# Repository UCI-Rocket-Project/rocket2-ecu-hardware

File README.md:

# rocket2's Engine Control Unit (ECU)
Documenation for ECU is hosted with MKDocs: [Click Here](https://uci-rocket-project.github.io/rocket2-ecu-hardware/)
  
# CAD

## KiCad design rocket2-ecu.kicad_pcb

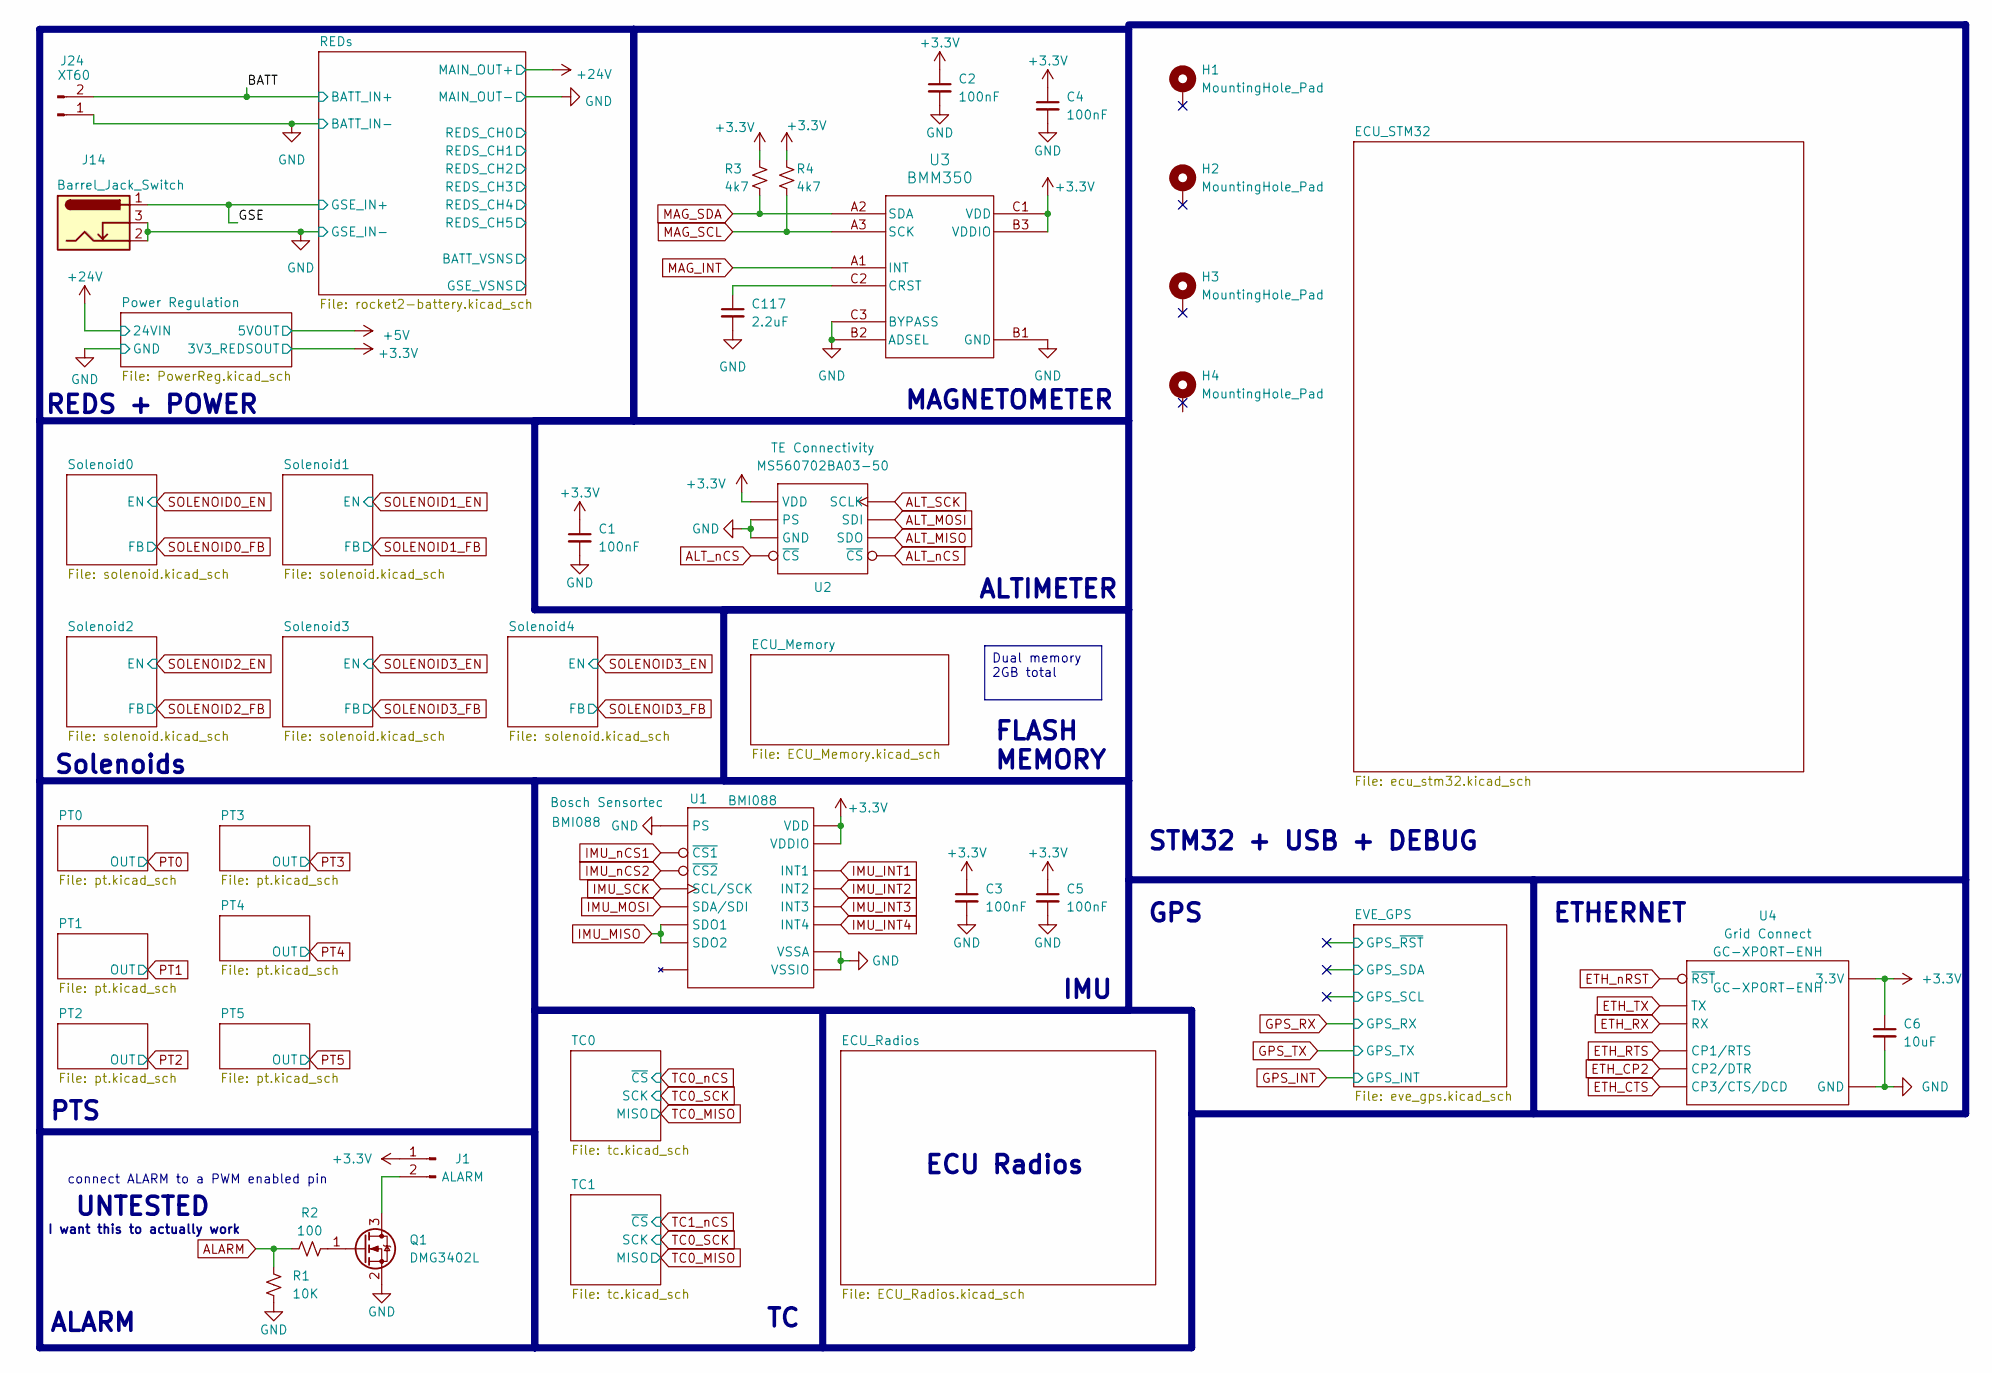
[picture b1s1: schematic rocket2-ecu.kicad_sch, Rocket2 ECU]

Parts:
C1, C2, C3, C4, C5: 100nF; C_0402_1005Metric; Part # Generic CAP CER 0.1UF 6.3V X7R 0402
C6: 10uF; C_0603_1608Metric; Part # Generic CAP CER 10UF 50V X7R 0603
C117: 2.2uF; C_0402_1005Metric; Part # Generic CAP CER 0.1UF 6.3V X7R 0402
H1, H2, H3, H4: MountingHole_Pad; MountingHole_4.3mm_M4_Pad_Via
J1: ALARM; Buzzer_TDK_PS1240P02BT_D12.2mm_H6.5mm; Part # CMI-0955-03TH
J14: Barrel_Jack_Switch; BarrelJack_Horizontal
J24: XT60; AMASS_XT60PW-M_1x02_P7.20mm_Horizontal
Q1: DMG3402L; SOT-23-3; Part # DMG3402L
R1: 10K; R_0402_1005Metric; Part # Generic RES SMD 10K OHM 1% 1/4W 0402
R2: 100; R_0402_1005Metric; Part # Generic RES SMD 100 OHM 1% 1/4W 0402
R3, R4: 4k7; R_0402_1005Metric; Part # Generic RES SMD 4.7K OHM 1% 1/4W 0402
U1: BMI088; Part # BMI088
U2: MS560702BA03-50; MS5607-02BA; Part # MS560702BA03-50
U3: BMM350
U4: GC-XPORT-ENH; GC-XPORT; Part # GC-XPORT-ENH

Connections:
+3.3V: C1.1, C2.1, C3.1, C4.1, C5.1, C6.1, J1.1, R3.1, R4.1, U1.3 (VDD), U1.11 (VDDIO), U2.1 (VDD), U3.B3 (VDDIO), U3.C1 (VDD), U4.2 (3.3V); also elsewhere on the board
/BATT: J24.2; also elsewhere on the board
/GSE: J14.1; also elsewhere on the board
ALARM: R1.2, R2.1; also elsewhere on the board
ALT_MISO: U2.6 (SDO); also elsewhere on the board
ALT_MOSI: U2.7 (SDI); also elsewhere on the board
ALT_SCK: U2.8 (SCLK); also elsewhere on the board
ALT_nCS: U2.4 (~CS), U2.5 (~CS); also elsewhere on the board
ETH_CP2: U4.7 (CP2/DTR); also elsewhere on the board
ETH_CTS: U4.8 (CP3/CTS/DCD); also elsewhere on the board
ETH_RTS: U4.6 (CP1/RTS); also elsewhere on the board
ETH_RX: U4.5 (RX); also elsewhere on the board
ETH_TX: U4.4 (TX); also elsewhere on the board
ETH_nRST: U4.3 (~RST); also elsewhere on the board
GND: C1.2, C2.2, C3.2, C4.2, C5.2, C6.2, C117.2, J14.2, J14.3, J24.1, Q1.2 (S), R1.1, U1.4 (VSSA), U1.6 (VSSIO), U1.7 (PS), U2.2 (PS), U2.3 (GND), U3.B1 (GND), U3.B2 (ADSEL), U3.C3 (BYPASS), U4.1 (GND); also elsewhere on the board
IMU_INT1: U1.16 (INT1); also elsewhere on the board
IMU_INT2: U1.1 (INT2); also elsewhere on the board
IMU_INT3: U1.12 (INT3); also elsewhere on the board
IMU_INT4: U1.13 (INT4); also elsewhere on the board
IMU_MISO: U1.10 (SDO2), U1.15 (SDO1); also elsewhere on the board
IMU_MOSI: U1.9 (SDA/SDI); also elsewhere on the board
IMU_SCK: U1.8 (SCL/SCK); also elsewhere on the board
IMU_nCS1: U1.14 (~CS1); also elsewhere on the board
IMU_nCS2: U1.5 (~CS2); also elsewhere on the board
MAG_INT: U3.A1 (INT); also elsewhere on the board
MAG_SCL: R4.2, U3.A3 (SCK); also elsewhere on the board
MAG_SDA: R3.2, U3.A2 (SDA); also elsewhere on the board
unnamed: J1.2, Q1.3 (D)
unnamed: Q1.1 (G), R2.2
unnamed: C117.1, U3.C2 (CRST)

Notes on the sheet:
connect ALARM to a PWM enabled pin
ECU Radios
ALTIMETER
GPS
Solenoids
REDS + POWER
FLASH MEMORY
MAGNETOMETER
STM32 + USB + DEBUG
UNTESTED
IMU
PTS
ETHERNET
I want this to actually work
ALARM
Dual memory 2GB total

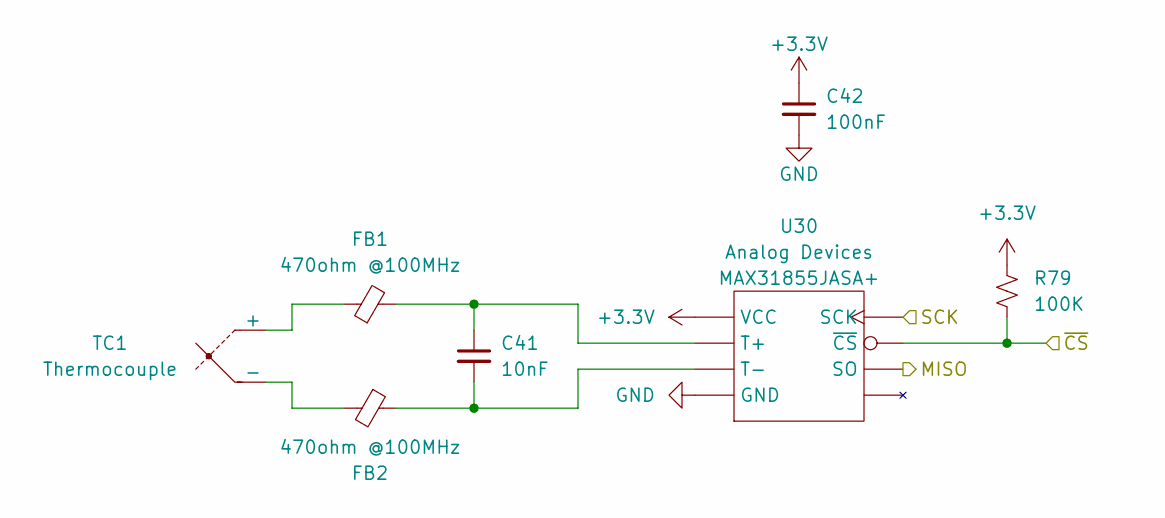
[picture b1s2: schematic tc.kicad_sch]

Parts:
C41: 10nF; C_0402_1005Metric; Part # Generic CAP CER 10NF 6.3V X7R 0402
C42: 100nF; C_0402_1005Metric; Part # Generic CAP CER 0.1UF 6.3V X7R 0402
FB1, FB2: 470ohm @100MHz; L_0603_1608Metric; Part # BLM18PG471SH1D
R79: 100K; R_0402_1005Metric; Part # Generic RES SMD 100K OHM 1% 1/16W 0402
TC1: Thermocouple; AM-K-PCB; Part # AM-K-PCB
U30: SOIC-8_3.9x4.9mm_P1.27mm; Part # MAX31855JASA+

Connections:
+3.3V: C42.1, R79.1, U30.4 (VCC); also elsewhere on the board
GND: C42.2, U30.1 (GND); also elsewhere on the board
unnamed: FB1.1, TC1.1 (+)
unnamed: FB2.2, TC1.2 (-)
unnamed: C41.1, FB1.2, U30.3 (T+)
unnamed: C41.2, FB2.1, U30.2 (T-)
TC0_MISO: U30.7 (SO); also elsewhere on the board
TC0_SCK: U30.5 (SCK); also elsewhere on the board
TC0_nCS: R79.2, U30.6 (~CS); also elsewhere on the board

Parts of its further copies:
C99: 10nF; C_0402_1005Metric; Part # Generic CAP CER 10NF 6.3V X7R 0402
C100: 100nF; C_0402_1005Metric; Part # Generic CAP CER 0.1UF 6.3V X7R 0402
FB3, FB4: 470ohm @100MHz; L_0603_1608Metric; Part # BLM18PG471SH1D
R124: 100K; R_0402_1005Metric; Part # Generic RES SMD 100K OHM 1% 1/16W 0402
TC2: Thermocouple; AM-K-PCB; Part # AM-K-PCB
U49: SOIC-8_3.9x4.9mm_P1.27mm; Part # MAX31855JASA+

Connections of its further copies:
+3.3V: C100.1, R124.1, U49.4 (VCC); also elsewhere on the board
GND: C100.2, U49.1 (GND); also elsewhere on the board
unnamed: FB3.1, TC2.1 (+)
unnamed: FB4.2, TC2.2 (-)
unnamed: C99.1, FB3.2, U49.3 (T+)
unnamed: C99.2, FB4.1, U49.2 (T-)
TC0_MISO: U49.7 (SO); also elsewhere on the board
TC0_SCK: U49.5 (SCK); also elsewhere on the board
TC1_nCS: R124.2, U49.6 (~CS); also elsewhere on the board

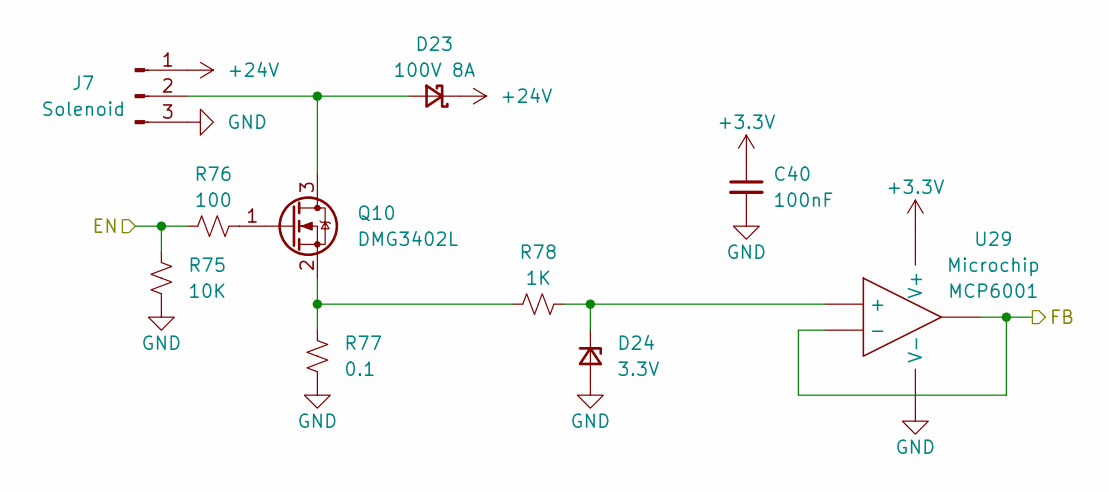
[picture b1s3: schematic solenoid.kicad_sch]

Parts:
C40: 100nF; C_0402_1005Metric; Part # Generic CAP CER 0.1UF 6.3V X7R 0402
D23: 100V 8A; D_PowerDI-5; Part # SDT8A100P5-7
D24: 3.3V; D_SOD-123; Part # MMSZ4684T1G
J7: Solenoid; GX-16 3 pin
Q10: DMG3402L; SOT-23-3; Part # DMG3402L
R75: 10K; R_0402_1005Metric; Part # Generic RES SMD 10K OHM 1% 1/4W 0402
R76: 100; R_0402_1005Metric; Part # Generic RES SMD 100 OHM 1% 1/4W 0402
R77: 0.1; R_2512_6332Metric; Part # CSRN2512FTR100
R78: 1K; R_0402_1005Metric; Part # Generic RES SMD 1K OHM 1% 1/16W 0402
U29: SOT-23-5; Part # MCP6001

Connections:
+3.3V: C40.1, U29.5 (V+); also elsewhere on the board
+24V: D23.1 (K), J7.1; also elsewhere on the board
GND: C40.2, D24.2 (A), J7.3, R75.1, R77.1, U29.2 (V-); also elsewhere on the board
unnamed: D23.2 (A), J7.2, Q10.3 (D)
unnamed: D24.1 (K), R78.2, U29.3 (+)
unnamed: Q10.1 (G), R76.2
unnamed: Q10.2 (S), R77.2, R78.1
SOLENOID0_EN: R75.2, R76.1; also elsewhere on the board
SOLENOID0_FB: U29.1, U29.4 (-); also elsewhere on the board

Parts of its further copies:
C8, C43, C48, C49: 100nF; C_0402_1005Metric; Part # Generic CAP CER 0.1UF 6.3V X7R 0402
D25, D27, D29, D41: 100V 8A; D_PowerDI-5; Part # SDT8A100P5-7
D26, D28, D30, D42: 3.3V; D_SOD-123; Part # MMSZ4684T1G
J8, J9, J10, J25: Solenoid; GX-16 3 pin
Q11, Q12, Q13, Q14: DMG3402L; SOT-23-3; Part # DMG3402L
R80, R86, R90, R131: 10K; R_0402_1005Metric; Part # Generic RES SMD 10K OHM 1% 1/4W 0402
R81, R87, R91, R132: 100; R_0402_1005Metric; Part # Generic RES SMD 100 OHM 1% 1/4W 0402
R82, R88, R92, R133: 0.1; R_2512_6332Metric; Part # CSRN2512FTR100
R83, R89, R93, R134: 1K; R_0402_1005Metric; Part # Generic RES SMD 1K OHM 1% 1/16W 0402
U31, U34, U35, U52: SOT-23-5; Part # MCP6001

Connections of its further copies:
+3.3V: C8.1, C43.1, C48.1, C49.1, U31.5 (V+), U34.5 (V+), U35.5 (V+), U52.5 (V+); also elsewhere on the board
+24V: D25.1 (K), D27.1 (K), D29.1 (K), D41.1 (K), J8.1, J9.1, J10.1, J25.1; also elsewhere on the board
GND: C8.2, C43.2, C48.2, C49.2, D26.2 (A), D28.2 (A), D30.2 (A), D42.2 (A), J8.3, J9.3, J10.3, J25.3, R80.1, R82.1, R86.1, R88.1, R90.1, R92.1, R131.1, R133.1, U31.2 (V-), U34.2 (V-), U35.2 (V-), U52.2 (V-); also elsewhere on the board
unnamed: D25.2 (A), J8.2, Q11.3 (D)
unnamed: D26.1 (K), R83.2, U31.3 (+)
unnamed: D27.2 (A), J9.2, Q12.3 (D)
unnamed: D28.1 (K), R89.2, U34.3 (+)
unnamed: D29.2 (A), J10.2, Q13.3 (D)
unnamed: D30.1 (K), R93.2, U35.3 (+)
unnamed: D41.2 (A), J25.2, Q14.3 (D)
unnamed: D42.1 (K), R134.2, U52.3 (+)
unnamed: Q11.1 (G), R81.2
unnamed: Q11.2 (S), R82.2, R83.1
unnamed: Q12.1 (G), R87.2
unnamed: Q12.2 (S), R88.2, R89.1
unnamed: Q13.1 (G), R91.2
unnamed: Q13.2 (S), R92.2, R93.1
unnamed: Q14.1 (G), R132.2
unnamed: Q14.2 (S), R133.2, R134.1
SOLENOID1_EN: R80.2, R81.1; also elsewhere on the board
SOLENOID1_FB: U31.1, U31.4 (-); also elsewhere on the board
SOLENOID2_EN: R86.2, R87.1; also elsewhere on the board
SOLENOID2_FB: U34.1, U34.4 (-); also elsewhere on the board
SOLENOID3_EN: R90.2, R91.1, R131.2, R132.1; also elsewhere on the board
SOLENOID3_FB: U35.1, U35.4 (-), U52.1, U52.4 (-); also elsewhere on the board

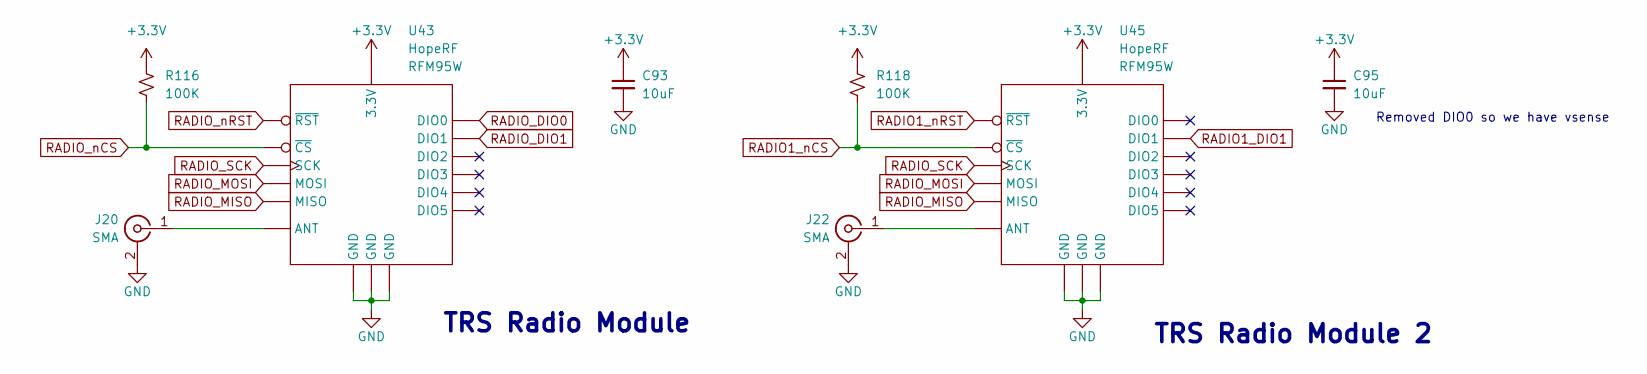
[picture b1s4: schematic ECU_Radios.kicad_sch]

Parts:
C93, C95: 10uF; C_0603_1608Metric; Part # Generic CAP CER 10UF 50V X7R 0603
J20, J22: SMA; SMA_Molex_73251-2200_Horizontal; Part # 0732512200
R116, R118: 100K; R_0402_1005Metric; Part # Generic RES SMD 100K OHM 1% 1/16W 0402
U43, U45: RFM95W; Part # RFM95W

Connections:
+3.3V: C93.1, C95.1, R116.1, R118.1, U43.13 (3.3V), U45.13 (3.3V); also elsewhere on the board
GND: C93.2, C95.2, J20.2 (Ext), J22.2 (Ext), U43.1 (GND), U43.8 (GND), U43.10 (GND), U45.1 (GND), U45.8 (GND), U45.10 (GND); also elsewhere on the board
unnamed: J20.1 (In), U43.9 (ANT)
unnamed: J22.1 (In), U45.9 (ANT)
RADIO1_DIO1: U45.15 (DIO1); also elsewhere on the board
RADIO1_nCS: R118.2, U45.5 (~CS); also elsewhere on the board
RADIO1_nRST: U45.6 (~RST); also elsewhere on the board
RADIO_DIO0: U43.14 (DIO0); also elsewhere on the board
RADIO_DIO1: U43.15 (DIO1); also elsewhere on the board
RADIO_MISO: U43.2 (MISO), U45.2 (MISO); also elsewhere on the board
RADIO_MOSI: U43.3 (MOSI), U45.3 (MOSI); also elsewhere on the board
RADIO_SCK: U43.4 (SCK), U45.4 (SCK); also elsewhere on the board
RADIO_nCS: R116.2, U43.5 (~CS); also elsewhere on the board
RADIO_nRST: U43.6 (~RST); also elsewhere on the board

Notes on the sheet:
TRS Radio Module 2
Removed DIO0 so we have vsense
TRS Radio Module

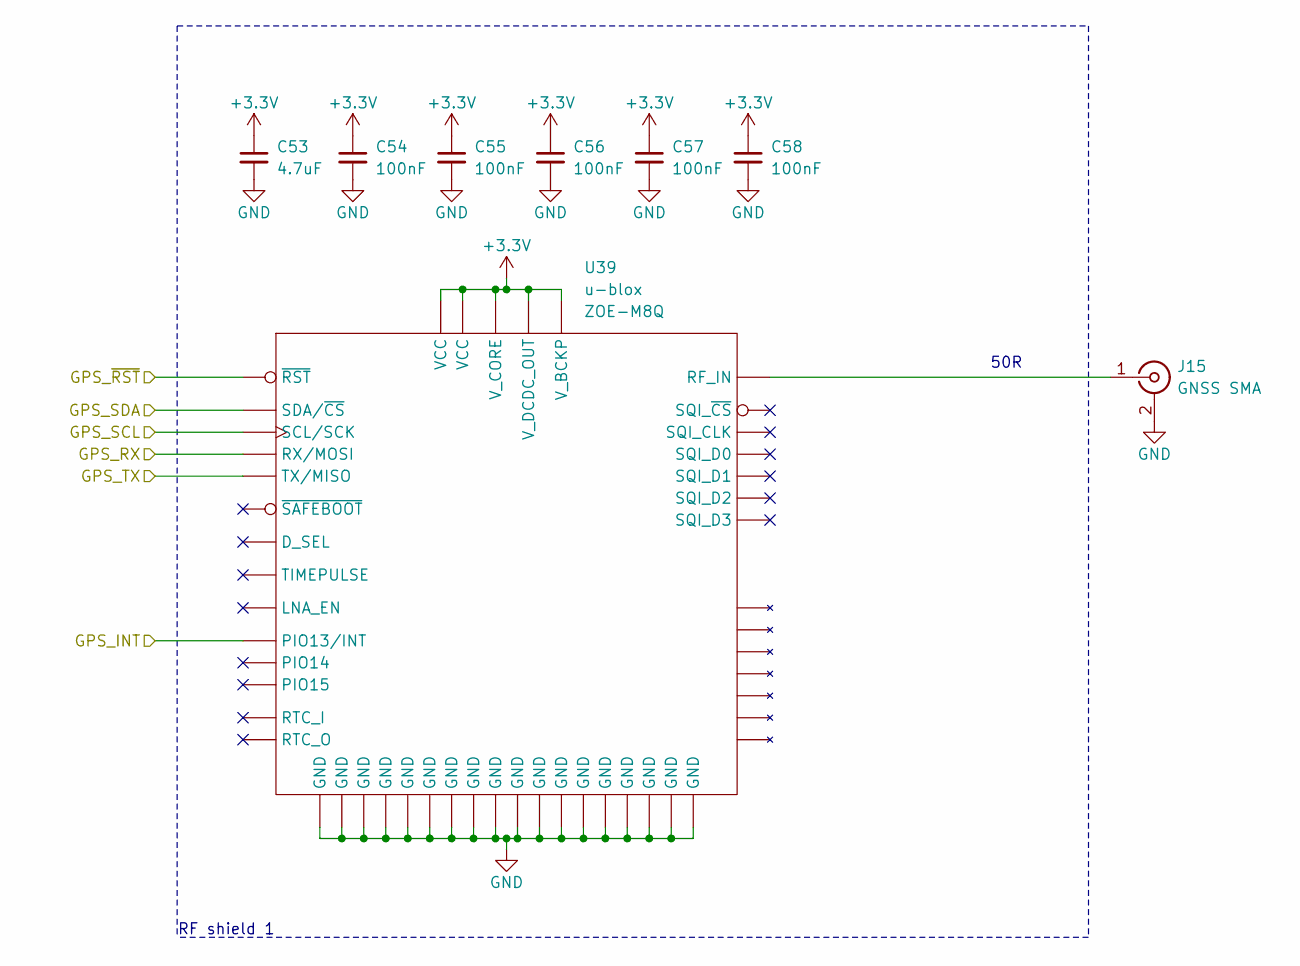
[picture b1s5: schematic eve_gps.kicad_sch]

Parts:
C53: 4.7uF; C_0603_1608Metric; Part # Generic CAP CER 4.7UF 6.3V X7R 0603
C54, C55, C56, C57, C58: 100nF; C_0402_1005Metric; Part # Generic CAP CER 0.1UF 6.3V X7R 0402
J15: GNSS SMA; SMA_Molex_73251-2200_Horizontal; Part # 0732512200
U39: ZOE-M8Q; Part # ZOE-M8Q

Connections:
+3.3V: C53.1, C54.1, C55.1, C56.1, C57.1, C58.1, U39.G1 (V_CORE), U39.H1 (V_DCDC_OUT), U39.H9 (V_BCKP), U39.J1 (VCC), U39.J2 (VCC); also elsewhere on the board
/EVE_GPS/GPS_SCL: U39.B1 (SCL/SCK)
/EVE_GPS/GPS_SDA: U39.A2 (SDA/~CS)
/EVE_GPS/GPS_~RST: U39.J6 (~RST)
GND: C53.2, C54.2, C55.2, C56.2, C57.2, C58.2, J15.2 (Ext), U39.A1 (GND), U39.A3 (GND), U39.A5 (GND), U39.A7 (GND), U39.A8 (GND), U39.A9 (GND), U39.B9 (GND), U39.C7 (GND), U39.C9 (GND), U39.D6 (GND), U39.D9 (GND), U39.E7 (GND), U39.F7 (GND), U39.G3 (GND), U39.G6 (GND), U39.G7 (GND), U39.J3 (GND), U39.J9 (GND); also elsewhere on the board
GPS_INT: U39.G4 (PIO13/INT); also elsewhere on the board
GPS_RX: U39.J4 (RX/MOSI); also elsewhere on the board
GPS_TX: U39.J5 (TX/MISO); also elsewhere on the board
unnamed: J15.1 (In), U39.A4 (RF_IN)

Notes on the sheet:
50R
RF shield 1

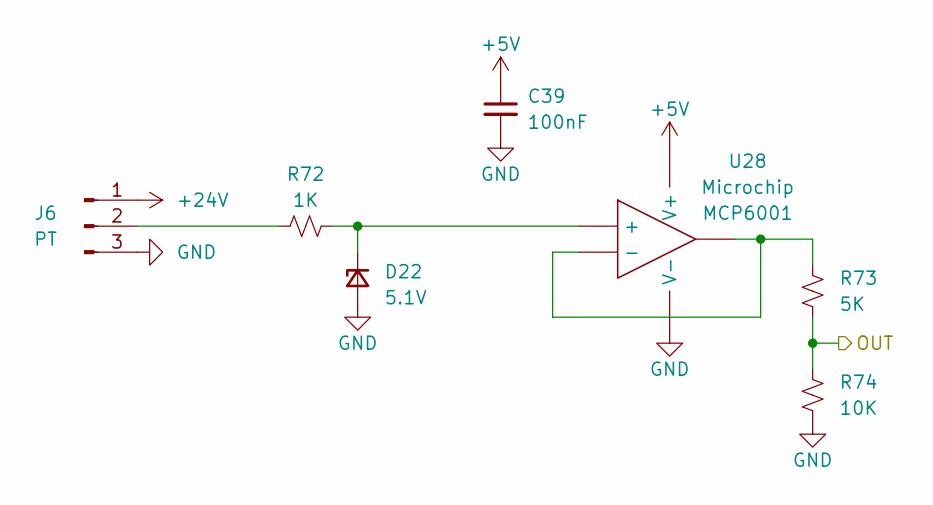
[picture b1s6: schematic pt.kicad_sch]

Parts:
C39: 100nF; C_0402_1005Metric; Part # Generic CAP CER 0.1UF 6.3V X7R 0402
D22: 5.1V; D_MiniMELF; Part # BZV55-B5V1
J6: PT; GX-12 3 pin
R72: 1K; R_0402_1005Metric; Part # Generic RES SMD 1K OHM 1% 1/16W 0402
R73: 5K; R_0402_1005Metric; Part # Generic RES SMD 5K OHM 0.1% 1/16W 0402
R74: 10K; R_0402_1005Metric; Part # Generic RES SMD 10K OHM 1% 1/4W 0402
U28: SOT-23-5; Part # MCP6001

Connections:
+5V: C39.1, U28.5 (V+); also elsewhere on the board
+24V: J6.1; also elsewhere on the board
GND: C39.2, D22.2 (A), J6.3, R74.1, U28.2 (V-); also elsewhere on the board
unnamed: D22.1 (K), R72.2, U28.3 (+)
unnamed: J6.2, R72.1
unnamed: R73.2, U28.1, U28.4 (-)
PT0: R73.1, R74.2; also elsewhere on the board

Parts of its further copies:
C50, C51, C52, C91, C92: 100nF; C_0402_1005Metric; Part # Generic CAP CER 0.1UF 6.3V X7R 0402
D31, D32, D33, D37, D38: 5.1V; D_MiniMELF; Part # BZV55-B5V1
J11, J12, J13, J18, J19: PT; GX-12 3 pin
R94, R97, R100, R110, R113: 1K; R_0402_1005Metric; Part # Generic RES SMD 1K OHM 1% 1/16W 0402
R95, R98, R101, R111, R114: 5K; R_0402_1005Metric; Part # Generic RES SMD 5K OHM 0.1% 1/16W 0402
R96, R99, R102, R112, R115: 10K; R_0402_1005Metric; Part # Generic RES SMD 10K OHM 1% 1/4W 0402
U36, U37, U38, U41, U42: SOT-23-5; Part # MCP6001

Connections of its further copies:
+5V: C50.1, C51.1, C52.1, C91.1, C92.1, U36.5 (V+), U37.5 (V+), U38.5 (V+), U41.5 (V+), U42.5 (V+); also elsewhere on the board
+24V: J11.1, J12.1, J13.1, J18.1, J19.1; also elsewhere on the board
GND: C50.2, C51.2, C52.2, C91.2, C92.2, D31.2 (A), D32.2 (A), D33.2 (A), D37.2 (A), D38.2 (A), J11.3, J12.3, J13.3, J18.3, J19.3, R96.1, R99.1, R102.1, R112.1, R115.1, U36.2 (V-), U37.2 (V-), U38.2 (V-), U41.2 (V-), U42.2 (V-); also elsewhere on the board
unnamed: D31.1 (K), R94.2, U36.3 (+)
unnamed: D32.1 (K), R97.2, U37.3 (+)
unnamed: D33.1 (K), R100.2, U38.3 (+)
unnamed: D37.1 (K), R110.2, U41.3 (+)
unnamed: D38.1 (K), R113.2, U42.3 (+)
unnamed: J11.2, R94.1
unnamed: J12.2, R97.1
unnamed: J13.2, R100.1
unnamed: J18.2, R110.1
unnamed: J19.2, R113.1
unnamed: R95.2, U36.1, U36.4 (-)
unnamed: R98.2, U37.1, U37.4 (-)
unnamed: R101.2, U38.1, U38.4 (-)
unnamed: R111.2, U41.1, U41.4 (-)
unnamed: R114.2, U42.1, U42.4 (-)
PT1: R95.1, R96.2; also elsewhere on the board
PT2: R98.1, R99.2; also elsewhere on the board
PT3: R101.1, R102.2; also elsewhere on the board
PT4: R111.1, R112.2; also elsewhere on the board
PT5: R114.1, R115.2; also elsewhere on the board

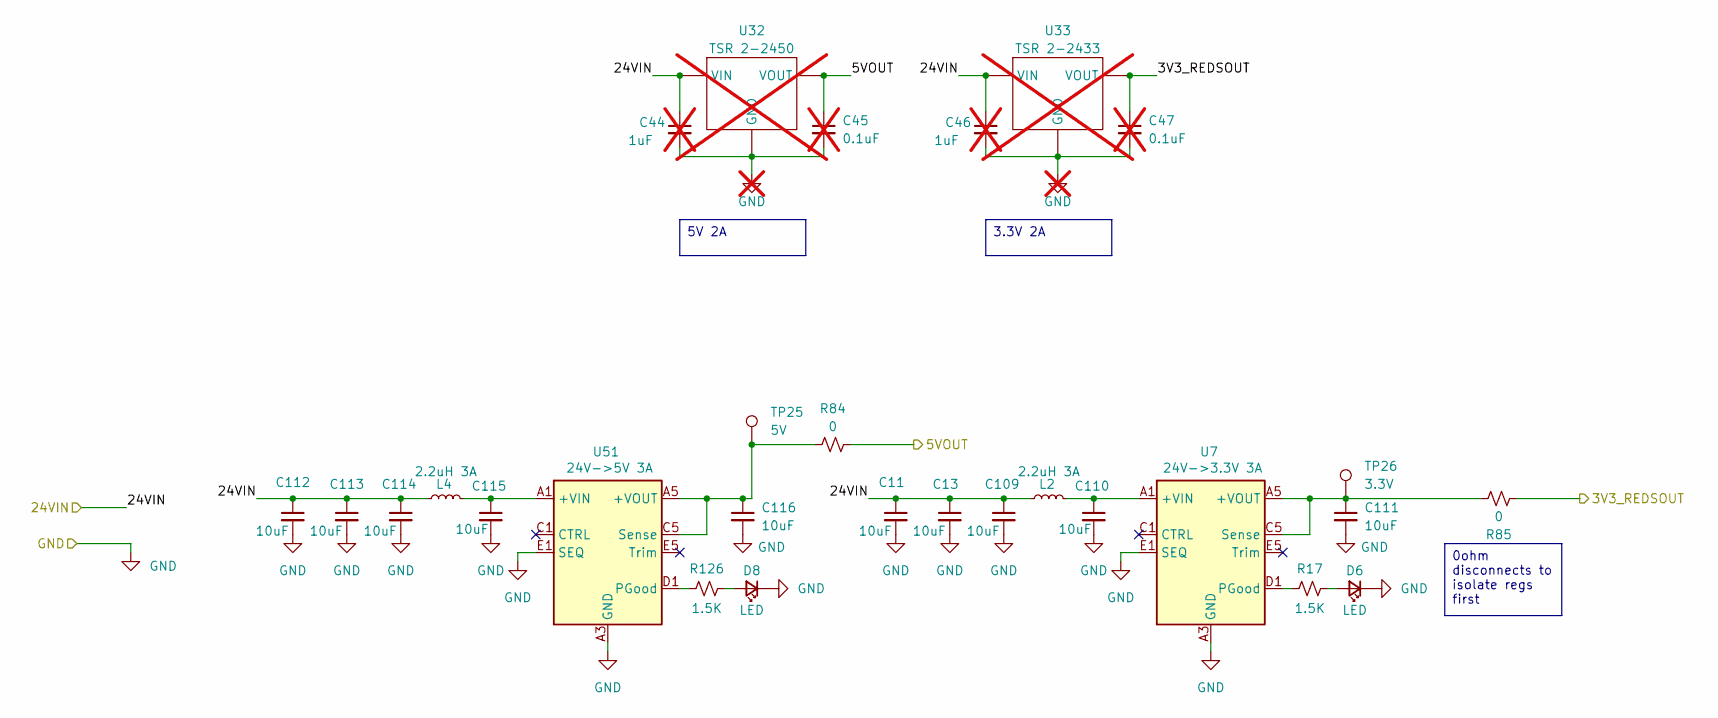
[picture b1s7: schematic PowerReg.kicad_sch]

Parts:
C11, C13, C109, C110, C112, C113, C114, C115: 10uF; C_1210_3225Metric; Part # Generic CAP CER 10UF 50V X7R 1210
C44, C46: 1uF; C_0603_1608Metric; Part # Generic CAP CER 1UF 50V X7R 0603; not fitted
C45, C47: 0.1uF; C_0603_1608Metric; Part # Generic CAP CER 0.1UF 6.3V X7R 0603; not fitted
C111, C116: 10uF; C_1206_3216Metric; Part # Generic CAP CER 10UF 25V X7R 1206
D6, D8: LED; LED_0603_1608Metric_Pad1.05x0.95mm_HandSolder; Part # Generic 0603 Yellow-Green LED
L2, L4: 2.2uH 3A; L_Vishay_IHLP-1212; Part # IHLP1212BZER2R2M11
R17, R126: 1.5K; R_0402_1005Metric; Part # Generic RES SMD 1.5K OHM 0.1% 1/16W 0402
R84, R85: 0; R_1206_3216Metric_Pad1.30x1.75mm_HandSolder; Part # Generic RES SMD 0 OHM 1206
TP25: 5V; TestPoint_Plated_Hole_D2.0mm
TP26: 3.3V; TestPoint_Plated_Hole_D2.0mm
U7: 24V->3.3V 3A; Converter_DCDC_RECOM_RPMx.x-x.0; Part # RPMB3.3-3.0
U32: Converter_DCDC_TRACO_TSR-1_THT; Part # TSR 2-2450; not fitted
U33: Converter_DCDC_TRACO_TSR-1_THT; Part # TSR 2-2433; not fitted
U51: 24V->5V 3A; Converter_DCDC_RECOM_RPMx.x-x.0; Part # RPMB5.0-3.0

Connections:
+3.3V: R85.2; also elsewhere on the board
+5V: R84.2; also elsewhere on the board
+24V: C11.1, C13.1, C44.1, C46.1, C109.1, C112.1, C113.1, C114.1, L2.1, L4.1, U32.1 (VIN), U33.1 (VIN); also elsewhere on the board
GND: C11.2, C13.2, C44.2, C45.2, C46.2, C47.2, C109.2, C110.2, C111.2, C112.2, C113.2, C114.2, C115.2, C116.2, D6.1 (K), D8.1 (K), U7.A3 (GND), U7.A4 (GND), U7.B1 (GND), U7.B2 (GND), U7.B3 (GND), U7.B4 (GND), U7.C2 (GND), U7.C3 (GND), U7.C4 (GND), U7.D2 (GND), U7.D3 (GND), U7.D4 (GND), U7.D5 (GND), U7.E1 (SEQ), U7.E3 (GND), U7.E4 (GND), U32.2 (GND), U33.2 (GND), U51.A3 (GND), U51.A4 (GND), U51.B1 (GND), U51.B2 (GND), U51.B3 (GND), U51.B4 (GND), U51.C2 (GND), U51.C3 (GND), U51.C4 (GND), U51.D2 (GND), U51.D3 (GND), U51.D4 (GND), U51.D5 (GND), U51.E1 (SEQ), U51.E3 (GND), U51.E4 (GND); also elsewhere on the board
unnamed: C45.1, U32.3 (VOUT)
unnamed: C47.1, U33.3 (VOUT)
unnamed: C110.1, L2.2, U7.A1 (+VIN), U7.A2 (+VIN)
unnamed: C115.1, L4.2, U51.A1 (+VIN), U51.A2 (+VIN)
unnamed: D6.2 (A), R17.2
unnamed: D8.2 (A), R126.2
unnamed: R17.1, U7.D1 (PGood)
unnamed: C111.1, R85.1, TP26.1, U7.A5 (+VOUT), U7.B5 (+VOUT), U7.C5 (Sense)
unnamed: R126.1, U51.D1 (PGood)
unnamed: C116.1, R84.1, TP25.1, U51.A5 (+VOUT), U51.B5 (+VOUT), U51.C5 (Sense)

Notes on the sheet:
3.3V 2A
5V 2A
0ohm disconnects to isolate regs first

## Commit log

2024-02-07 Rename files
2024-02-07 Add PCB outline
2024-03-06 Initial setup
2024-03-11 Lots of cleanup and updates; Waiting on PR approval for GPS filter
2024-03-24 changed usb-c, re-named and added some pins
2024-03-26 fixes based on REDs testing
2024-03-30 added pin assignments to components on existing schematic
2024-05-16 Updated so only STM pins left really
2024-05-22 added capacitors and resolved all comments
2024-05-24 added oscillator
2024-05-25 fixed somwe stuff
2024-05-26 added flash memory and ldos
2024-05-27 Added stat sense in REDs; kicad V8.01
2024-06-07 8.02 Update; Also changed VRMs and added some notes
2024-10-30 ECU essentially reviewable
2024-10-30 Removed temp files
2024-11-16 addressed PR comments
2024-11-30 Updated schematic with IOC
2024-12-02 Moved PTs to ADC pins
2024-12-03 Assigned almost all footprints
2024-12-05 Started layout
2024-12-17 Started putting it all together
2024-12-19 More layout updates
2024-12-23 Replaced Regs
2024-12-23 made reg circuits
2024-12-26 All parts on board, starting routing
2024-12-27 Lots of routing
2024-12-27 More routing, only GPS and REDS radio left
2024-12-27 Finished layout
2024-12-27 Added mounting holes
2024-12-30 Updated with Daniels suggestions
2025-01-01 Added buzzer
2025-01-07 resolved continuous ground issues
2025-01-08 new BOM
2025-01-09 notes
2025-01-09 Addressed comments; See issue for notes
2025-01-09 Fixed groundstiching and pad sizes
2025-01-10 Finished
2025-01-10 Fully up to date
2025-01-10 Added back UCIRP logo
2025-11-13 REDS updated with diodes and hierarchy to main micro
2025-11-13 Updated REDS for working
2025-11-16 Added power sense to rocket2-battery with voltage follower, added +1 solenoids and PT circuit, made new gx connectors
2025-11-16 moved from bmm150 to bmm350
2025-11-16 idk what I changed tbh
2025-11-17 Component placement halfway done
2025-11-20 Placed radios
2025-11-21 3/4 DC-DC converters done
2025-11-22 power connectors done
2025-11-22 ALMOST DONE WITH PLACEMENT
2025-11-22 more routing, 25% done
2025-11-24 ALMOST
2025-11-24 layout done
2025-11-24 Added IOC file
2025-11-24 Fixed DRC errors
2025-11-25 Moved SWD to front face
2025-11-25 Moved all LEDS to front (i think)
2025-12-01 Deleted 5V, edited LPFs on TCs and PTs
2025-12-02 updating 3d cad, not done
2025-12-02 CAD almost done, missing gx connectors
2025-12-02 CAD completely done
2025-12-12 version in PCBway 12/12/2025
2025-12-14 added .ioc file
2025-12-26 added some production files
2026-01-12 changed charging circuit for Insta360, gonna send in now on JLCPCB
2026-01-25 Change header level for author name in README
2026-04-16 added ecu adapter board submodule
2026-04-19 ecu docs
2026-04-19 fixing docs sruture
2026-04-19 fixed structureq again
2026-04-19 github workflow for mkdocs
2026-04-19 testing docs edits
2026-04-19 Deployed 6c27b1e with MkDocs version: 1.6.1
2026-04-28 added bring-up test plan and current ecu hardware bring-up updates
2026-04-30 Reformatted file structure
2026-05-05 Revise README for Rocket2's ECU documentation
    Updated the README to reflect the new project name and documentation link, and removed unnecessary HTML tags.
2026-05-05 Fix README title casing and correct documentation link
2026-05-05 fixed connector system description and updated bring-up log
2026-05-05 Deployed bb630e8 with MkDocs version: 1.6.1
